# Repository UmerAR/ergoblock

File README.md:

# ErgoBlock
A wired split 3x6 column staggered keyboards with 3 thumb keys, an aggressive pinkie stagger, and low profile switches
PCB is also reversible

maybe next keyboard i'll make it wireless
## Keymap
QWERTY layout with home row mods and a custom symbol and navigation layer. stuck with qwerty since I'm still in school, might switch to something more efficient in the future.

## Parts
PCB was designed in KiCad using Ergogen and ordered using JLCPCB
All other parts were ordered from AliExpress
| Parts                        |Price ($)| Link                                                             |
|------------------------------|---------|------------------------------------------------------------------|
|PCB                           |  16.57  |[JLCPCB](jlcpcb.com)                                              |
|Keycaps (50pc)                |  21.56  |[AliExpress](https://vi.aliexpress.com/item/1005006734545486.html)|
|hotswap sockets (10pc) x5     |  5.15   |[AliExpress](https://vi.aliexpress.com/item/32901654130.html)     |
|Kalih pro red switches (70pcs)|  27.75  |[AliExpress](https://vi.aliexpress.com/item/1005005723938995.html)|
|diodes (100pc)                |  1.31   |[AliExpress](https://vi.aliexpress.com/item/4000685043735.html)   |
|trrs jack (10pc)              |  1.21   |[AliExpress](https://vi.aliexpress.com/item/1005003111662179.html)|
|reset switch 4*4*1.5 (20pc)   |  2.83   |[AliExpress](https://vi.aliexpress.com/item/1005005924012567.html)|
|promicro x2                   |  8.70   |[AliExpress](https://vi.aliexpress.com/item/1005006654641959.html)|
|total                         |  85.08  |

## Author
- [@UmerAR](https://github.com/UmerAR)

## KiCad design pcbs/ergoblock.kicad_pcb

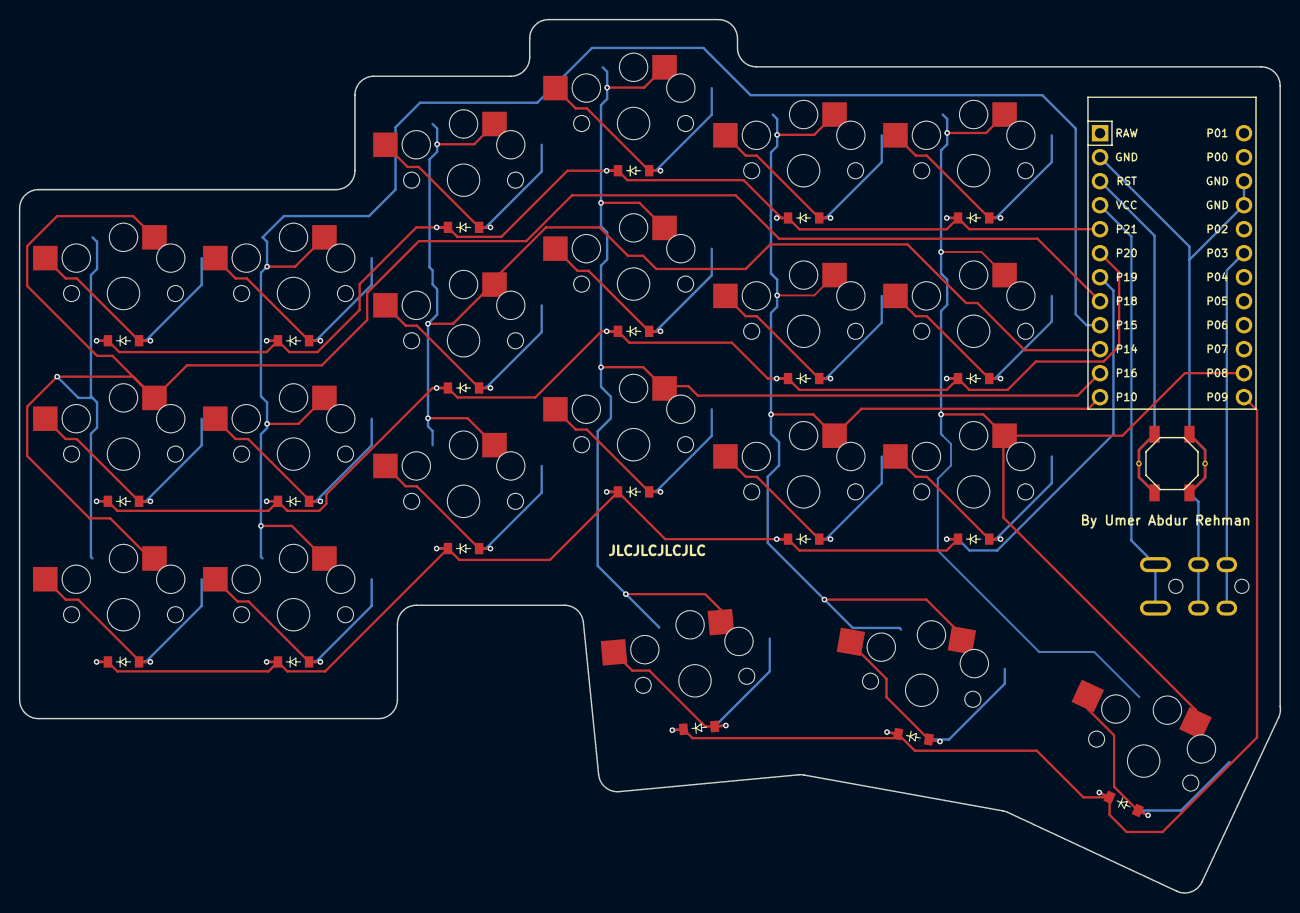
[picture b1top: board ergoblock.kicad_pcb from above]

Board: 2 copper layers, 133.5 x 92.5 mm, 46 parts (0 on the bottom side), 35 nets.

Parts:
B1, B2: SW_TACT_ALPS_SKQGABE010
D1, D2, D3, D4, D5, D6, D7, D8, D9, D10, D11, D12, D13, D14, D15, D16, D17, D18, D19, D20, D21: diode_tht_sod123
MCU1: ProMicro
S1, S2, S3, S4, S5, S6, S7, S8, S9, S10, S11, S12, S13, S14, S15, S16, S17, S18, S19, S20, S21: PG1350
TRRS1: trrs_pj320a (reversible, symmetric)

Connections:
GND: B1.1, B2.1, MCU1.2, MCU1.15, MCU1.16, TRRS1.3
P3: MCU1.18, TRRS1.2
P8: MCU1.23, S16.1, S17.1, S18.1, S21.1
P9: D19.1, D20.1, D21.1, MCU1.24
P10: MCU1.12, S13.1, S14.1, S15.1, S20.1
P14: MCU1.10, S7.1, S8.1, S9.1
P15: MCU1.9, S4.1, S5.1, S6.1
P16: MCU1.11, S10.1, S11.1, S12.1, S19.1
P18: MCU1.8, S1.1, S2.1, S3.1
P19: D1.1, D4.1, D7.1, D10.1, D13.1, D16.1, MCU1.7
P20: D2.1, D5.1, D8.1, D11.1, D14.1, D17.1, MCU1.6
P21: D3.1, D6.1, D9.1, D12.1, D15.1, D18.1, MCU1.5
RST: B1.2, B2.2, MCU1.3
VCC: MCU1.4, TRRS1.4
index_bottom: D13.2, S13.2
index_home: D14.2, S14.2
index_top: D15.2, S15.2
inner_bottom: D16.2, S16.2
inner_cluster: D21.2, S21.2
inner_home: D17.2, S17.2
inner_top: D18.2, S18.2
middle_bottom: D10.2, S10.2
middle_cluster: D20.2, S20.2
middle_home: D11.2, S11.2
middle_top: D12.2, S12.2
outer_bottom: D1.2, S1.2
outer_cluster: D19.2, S19.2
outer_home: D2.2, S2.2
outer_top: D3.2, S3.2
pinkie_bottom: D4.2, S4.2
pinkie_home: D5.2, S5.2
pinkie_top: D6.2, S6.2
ring_bottom: D7.2, S7.2
ring_home: D8.2, S8.2
ring_top: D9.2, S9.2

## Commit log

2025-02-05 Added Keyboard and PCB design Files
2025-02-05 Added PCB design files and keyboard design files
2025-02-05 Create firmware folder
2025-02-05 added qmk firmware and keymaps
2025-02-05 Create images folder
2025-02-05 added image
2025-02-05 uploaded keymap image
2025-03-29 fixed wakeup issue with firmware
2025-04-13 some changes
2025-04-13 too fast
2025-04-20 fixed image
2026-05-22 fixed firmware
